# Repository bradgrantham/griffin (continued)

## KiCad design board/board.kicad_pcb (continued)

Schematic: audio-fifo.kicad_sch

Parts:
C36, C37, C38, C39: 100nF; C_Disc_D5.0mm_W2.5mm_P5.00mm
R35, R36, R37, R38, R150, R151, R152, R153: 0R; R_Axial_DIN0207_L6.3mm_D2.5mm_P10.16mm_Horizontal
TP3, TP4, TP5, TP6: TestPoint; TestPoint_Pad_D1.5mm
U25, U26, U30, U31: IDT7200L15P; DIP-28_W7.62mm

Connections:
+5V: C36.1, C37.1, C38.1, C39.1, U25.23 (FL), U25.28 (VCC), U26.23 (FL), U26.28 (VCC), U30.23 (FL), U30.28 (VCC), U31.23 (FL), U31.28 (VCC); also elsewhere on the board
/AUDIO_FIFO/~SAMPLES0_FIFO_W_FIFO_SIDE: R150.2, U25.1 (WR)
/AUDIO_FIFO/~SAMPLES1_FIFO_W_FIFO_SIDE: R151.2, U26.1 (WR)
/AUDIO_FIFO/~SAMPLES2_FIFO_W_FIFO_SIDE: R152.2, U30.1 (WR)
/AUDIO_FIFO/~SAMPLES3_FIFO_W_FIFO_SIDE: R153.2, U31.1 (WR)
D_AUDIO_FIFO0: U30.6 (D0), U31.6 (D0); also elsewhere on the board
D_AUDIO_FIFO1: U30.5 (D1), U31.5 (D1); also elsewhere on the board
D_AUDIO_FIFO2: U30.4 (D2), U31.4 (D2); also elsewhere on the board
D_AUDIO_FIFO3: U30.3 (D3), U31.3 (D3); also elsewhere on the board
D_AUDIO_FIFO4: U30.27 (D4), U31.27 (D4); also elsewhere on the board
D_AUDIO_FIFO5: U30.26 (D5), U31.26 (D5); also elsewhere on the board
D_AUDIO_FIFO6: U30.25 (D6), U31.25 (D6); also elsewhere on the board
D_AUDIO_FIFO7: U30.24 (D7), U31.24 (D7); also elsewhere on the board
D_AUDIO_FIFO8: U25.6 (D0), U26.6 (D0); also elsewhere on the board
D_AUDIO_FIFO9: U25.5 (D1), U26.5 (D1); also elsewhere on the board
D_AUDIO_FIFO10: U25.4 (D2), U26.4 (D2); also elsewhere on the board
D_AUDIO_FIFO11: U25.3 (D3), U26.3 (D3); also elsewhere on the board
D_AUDIO_FIFO12: U25.27 (D4), U26.27 (D4); also elsewhere on the board
D_AUDIO_FIFO13: U25.26 (D5), U26.26 (D5); also elsewhere on the board
D_AUDIO_FIFO14: U25.25 (D6), U26.25 (D6); also elsewhere on the board
D_AUDIO_FIFO15: U25.24 (D7), U26.24 (D7); also elsewhere on the board
GND: C36.2, C37.2, C38.2, C39.2, U25.2 (D8), U25.7 (XI), U25.14 (VSS), U26.2 (D8), U26.7 (XI), U26.14 (VSS), U30.2 (D8), U30.7 (XI), U30.14 (VSS), U31.2 (D8), U31.7 (XI), U31.14 (VSS); also elsewhere on the board
unnamed: R35.1, U25.15 (RD)
unnamed: R36.1, U26.15 (RD)
unnamed: R37.1, U30.15 (RD)
unnamed: R38.1, U31.15 (RD)
SAMPLE0_Q0: U25.9 (Q0); also elsewhere on the board
SAMPLE0_Q1: U25.10 (Q1); also elsewhere on the board
SAMPLE0_Q2: U25.11 (Q2); also elsewhere on the board
SAMPLE0_Q3: U25.12 (Q3); also elsewhere on the board
SAMPLE0_Q4: U25.16 (Q4); also elsewhere on the board
SAMPLE0_Q5: U25.17 (Q5); also elsewhere on the board
SAMPLE0_Q6: U25.18 (Q6); also elsewhere on the board
SAMPLE0_Q7: U25.19 (Q7); also elsewhere on the board
SAMPLE1_Q0: U26.9 (Q0); also elsewhere on the board
SAMPLE1_Q1: U26.10 (Q1); also elsewhere on the board
SAMPLE1_Q2: U26.11 (Q2); also elsewhere on the board
SAMPLE1_Q3: U26.12 (Q3); also elsewhere on the board
SAMPLE1_Q4: U26.16 (Q4); also elsewhere on the board
SAMPLE1_Q5: U26.17 (Q5); also elsewhere on the board
SAMPLE1_Q6: U26.18 (Q6); also elsewhere on the board
SAMPLE1_Q7: U26.19 (Q7); also elsewhere on the board
SAMPLE2_Q0: U30.9 (Q0); also elsewhere on the board
SAMPLE2_Q1: U30.10 (Q1); also elsewhere on the board
SAMPLE2_Q2: U30.11 (Q2); also elsewhere on the board
SAMPLE2_Q3: U30.12 (Q3); also elsewhere on the board
SAMPLE2_Q4: U30.16 (Q4); also elsewhere on the board
SAMPLE2_Q5: U30.17 (Q5); also elsewhere on the board
SAMPLE2_Q6: U30.18 (Q6); also elsewhere on the board
SAMPLE2_Q7: U30.19 (Q7); also elsewhere on the board
SAMPLE3_Q0: U31.9 (Q0); also elsewhere on the board
SAMPLE3_Q1: U31.10 (Q1); also elsewhere on the board
SAMPLE3_Q2: U31.11 (Q2); also elsewhere on the board
SAMPLE3_Q3: U31.12 (Q3); also elsewhere on the board
SAMPLE3_Q4: U31.16 (Q4); also elsewhere on the board
SAMPLE3_Q5: U31.17 (Q5); also elsewhere on the board
SAMPLE3_Q6: U31.18 (Q6); also elsewhere on the board
SAMPLE3_Q7: U31.19 (Q7); also elsewhere on the board
~RESET: U25.22 (CLR), U26.22 (CLR), U30.22 (CLR), U31.22 (CLR); also elsewhere on the board
~SAMPLES0_FIFO_W: R150.1; also elsewhere on the board
~SAMPLES1_FIFO_W: R151.1; also elsewhere on the board
~SAMPLES2_FIFO_W: R152.1; also elsewhere on the board
~SAMPLES3_FIFO_W: R153.1; also elsewhere on the board
~SAMPLE_EF0: TP3.1, U25.21 (EF); also elsewhere on the board
~SAMPLE_EF1: TP4.1, U26.21 (EF); also elsewhere on the board
~SAMPLE_EF2: TP5.1, U30.21 (EF); also elsewhere on the board
~SAMPLE_EF3: TP6.1, U31.21 (EF); also elsewhere on the board
~SAMPLE_R0: R35.2; also elsewhere on the board
~SAMPLE_R1: R36.2; also elsewhere on the board
~SAMPLE_R2: R37.2; also elsewhere on the board
~SAMPLE_R3: R38.2; also elsewhere on the board

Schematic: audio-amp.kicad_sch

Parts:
C57, C59, C61: 47nF; C_Rect_L7.2mm_W2.5mm_P5.00mm
C58, C60, C62: 250uF; CP_Radial_D8.0mm_P3.50mm
C65, C66, C67: 100nF; C_Disc_D5.0mm_W2.5mm_P5.00mm
J6: 3.5mm stereo, tip+ring NC switches (part TBD: SJ3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
J16: VOLUME POT (dual 10kA, panel); PinHeader_1x06_P2.54mm_Vertical
J17: SPEAKER 8 ohm (case); PinHeader_1x02_P2.54mm_Vertical
R91, R94: 10k; R_Axial_DIN0207_L6.3mm_D2.5mm_P10.16mm_Horizontal
R92, R95, R99: 1k; R_Axial_DIN0207_L6.3mm_D2.5mm_P10.16mm_Horizontal
R93, R96, R154: 10R; R_Axial_DIN0207_L6.3mm_D2.5mm_P10.16mm_Horizontal
R97, R98: 47k; R_Axial_DIN0207_L6.3mm_D2.5mm_P10.16mm_Horizontal
U33, U34, U35: LM386; DIP-8_W7.62mm

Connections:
+5V: C65.1, C66.1, C67.1, U33.6 (V+), U34.6 (V+), U35.6 (V+); also elsewhere on the board
/AUDIO_AMP/HP_AMP_L: C58.1, R93.1, U33.5
/AUDIO_AMP/HP_AMP_R: C60.1, R96.1, U34.5
/AUDIO_AMP/HP_IN_L: R91.2, R92.1, U33.3 (+)
/AUDIO_AMP/HP_IN_R: R94.2, R95.1, U34.3 (+)
/AUDIO_AMP/POT_L: J16.2, R91.1
/AUDIO_AMP/POT_R: J16.5, R94.1
/AUDIO_AMP/SPK_AMP: C62.1, R154.1, U35.5
/AUDIO_AMP/SPK_IN_L: J6.TN, R97.1
/AUDIO_AMP/SPK_IN_R: J6.RN, R98.1
/AUDIO_AMP/SPK_PLUS: C62.2, J17.1
/AUDIO_AMP/SPK_SUM: R97.2, R98.2, R99.1, U35.3 (+)
/AUDIO_AMP/ZOB_L: C57.1, R93.2
/AUDIO_AMP/ZOB_R: C59.1, R96.2
/AUDIO_AMP/ZOB_SPK: C61.1, R154.2
GND: C57.2, C59.2, C61.2, C65.2, C66.2, C67.2, J6.S, J16.3, J16.6, J17.2, R92.2, R95.2, R99.2, U33.2 (-), U33.4 (GND), U34.2 (-), U34.4 (GND), U35.2 (-), U35.4 (GND); also elsewhere on the board
HP_L: C58.2, J6.T
HP_R: C60.2, J6.R
LINE_L: J16.1; also elsewhere on the board
LINE_R: J16.4; also elsewhere on the board

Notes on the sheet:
Inserting a plug opens TN/RN and mutes the speaker; software mute = VOLUME 0 on all four channels (griffin.yml).
C65, C66, C67 bypass U33, U34, U35. R154 is the speaker Zobel 10R.
J16: dual-gang 10k audio taper, element top = LINE, bottom = GND, wiper out; panel part on a header.

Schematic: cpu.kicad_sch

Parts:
C2, C3: 100nF; C_Disc_D5.0mm_W2.5mm_P5.00mm
R4, R5, R6, R8, R9, R10, R11, R12, R13, R14: 10K; R_Axial_DIN0207_L6.3mm_D2.5mm_P10.16mm_Horizontal
R7: 4.7K; R_Axial_DIN0207_L6.3mm_D2.5mm_P10.16mm_Horizontal
U2: MC68000; DIP-64_W22.86mm

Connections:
+5V: C2.1, C3.1, R4.1, R5.1, R6.1, R7.1, R8.1, R9.1, R10.1, R11.1, R12.1, R13.1, R14.1, U2.14 (V_{CC}), U2.49 (V_{CC}); also elsewhere on the board
A1: U2.29 (A1); also elsewhere on the board
A2: U2.30 (A2); also elsewhere on the board
A3: U2.31 (A3); also elsewhere on the board
A4: U2.32 (A4); also elsewhere on the board
A5: U2.33 (A5); also elsewhere on the board
A6: U2.34 (A6); also elsewhere on the board
A7: U2.35 (A7); also elsewhere on the board
A8: U2.36 (A8); also elsewhere on the board
A9: U2.37 (A9); also elsewhere on the board
A10: U2.38 (A10); also elsewhere on the board
A11: U2.39 (A11); also elsewhere on the board
A12: U2.40 (A12); also elsewhere on the board
A13: U2.41 (A13); also elsewhere on the board
A14: U2.42 (A14); also elsewhere on the board
A15: U2.43 (A15); also elsewhere on the board
A16: U2.44 (A16); also elsewhere on the board
A17: U2.45 (A17); also elsewhere on the board
A18: U2.46 (A18); also elsewhere on the board
A19: U2.47 (A19); also elsewhere on the board
A20: U2.48 (A20); also elsewhere on the board
A21: U2.50 (A21); also elsewhere on the board
A22: U2.51 (A22); also elsewhere on the board
A23: U2.52 (A23); also elsewhere on the board
D0: U2.5 (D0); also elsewhere on the board
D1: U2.4 (D1); also elsewhere on the board
D2: U2.3 (D2); also elsewhere on the board
D3: U2.2 (D3); also elsewhere on the board
D4: U2.1 (D4); also elsewhere on the board
D5: U2.64 (D5); also elsewhere on the board
D6: U2.63 (D6); also elsewhere on the board
D7: U2.62 (D7); also elsewhere on the board
D8: U2.61 (D8); also elsewhere on the board
D9: U2.60 (D9); also elsewhere on the board
D10: U2.59 (D10); also elsewhere on the board
D11: U2.58 (D11); also elsewhere on the board
D12: U2.57 (D12); also elsewhere on the board
D13: U2.56 (D13); also elsewhere on the board
D14: U2.55 (D14); also elsewhere on the board
D15: U2.54 (D15); also elsewhere on the board
FC0: R6.2, U2.28 (FC0); also elsewhere on the board
FC1: R9.2, U2.27 (FC1); also elsewhere on the board
FC2: R11.2, U2.26 (FC2); also elsewhere on the board
GND: C2.2, C3.2, U2.16 (GND), U2.53 (GND); also elsewhere on the board
R/~W: R10.2, U2.9 (R/~W); also elsewhere on the board
SYSCLK: U2.15 (CLK); also elsewhere on the board
~AS: R8.2, U2.6 (~AS); also elsewhere on the board
~BERR: U2.22 (~BERR); also elsewhere on the board
~BGACK: R5.2, U2.12 (~BGACK); also elsewhere on the board
~BG: U2.11 (~BG); also elsewhere on the board
~BR: R4.2, U2.13 (~BR); also elsewhere on the board
~DTACK: U2.10 (~DTACK); also elsewhere on the board
~HALT: R7.2, U2.17 (~HALT); also elsewhere on the board
~IPL0: U2.25 (~IPL0); also elsewhere on the board
~IPL1: U2.24 (~IPL1); also elsewhere on the board
~IPL2: U2.23 (~IPL2); also elsewhere on the board
~LDS: R13.2, U2.8 (~LDS); also elsewhere on the board
~RESET: U2.18 (~RESET); also elsewhere on the board
~UDS: R12.2, U2.7 (~UDS); also elsewhere on the board
~VPA: R14.2, U2.21 (~VPA); also elsewhere on the board

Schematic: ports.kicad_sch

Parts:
C17: 100nF; C_Disc_D5.0mm_W2.5mm_P5.00mm
J13: PORTS SPARE; PinHeader_1x03_P2.54mm_Vertical
U14: PORTS; PLCC-84_THT-Socket

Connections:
+5V: C17.1, U14.3 (VCCINT), U14.13 (VCCIO), U14.26 (VCCIO), U14.38 (VCCIO), U14.43 (VCCINT), U14.53 (VCCIO), U14.66 (VCCIO), U14.78 (VCCIO); also elsewhere on the board
/PORTS/PORTS_SPARE_34: J13.1, U14.34 (I/O)
/PORTS/PORTS_SPARE_41: J13.2, U14.41 (I/O)
A1: U14.31 (I/O); also elsewhere on the board
A2: U14.30 (I/O); also elsewhere on the board
A3: U14.21 (I/O); also elsewhere on the board
A4: U14.22 (I/O); also elsewhere on the board
D0: U14.18 (I/O); also elsewhere on the board
D1: U14.16 (I/O); also elsewhere on the board
D2: U14.15 (I/O); also elsewhere on the board
D3: U14.28 (I/O); also elsewhere on the board
D4: U14.24 (I/O); also elsewhere on the board
D5: U14.27 (I/O); also elsewhere on the board
D6: U14.20 (I/O); also elsewhere on the board
D7: U14.29 (I/O); also elsewhere on the board
GLUE_TO_PORTS_TD: U14.14 (I/O/TDI); also elsewhere on the board
GND: C17.2, J13.3, U14.7 (GND), U14.19 (GND), U14.32 (GND), U14.42 (GND), U14.47 (GND), U14.59 (GND), U14.72 (GND), U14.82 (GND); also elsewhere on the board
JOYSTICK_1_DOWN: U14.12 (I/O/PD1); also elsewhere on the board
JOYSTICK_1_FIRE: U14.40 (I/O); also elsewhere on the board
JOYSTICK_1_LEFT: U14.51 (I/O); also elsewhere on the board
JOYSTICK_1_PIN5: U14.5 (I/O); also elsewhere on the board
JOYSTICK_1_PIN9: U14.39 (I/O); also elsewhere on the board
JOYSTICK_1_RIGHT: U14.35 (I/O); also elsewhere on the board
JOYSTICK_1_UP: U14.9 (I/O); also elsewhere on the board
JOYSTICK_2_DOWN: U14.11 (I/O); also elsewhere on the board
JOYSTICK_2_FIRE: U14.4 (I/O); also elsewhere on the board
JOYSTICK_2_LEFT: U14.50 (I/O); also elsewhere on the board
JOYSTICK_2_PIN5: U14.8 (I/O); also elsewhere on the board
JOYSTICK_2_PIN9: U14.37 (I/O); also elsewhere on the board
JOYSTICK_2_RIGHT: U14.36 (I/O); also elsewhere on the board
JOYSTICK_2_UP: U14.10 (I/O); also elsewhere on the board
JTAG_TCK: U14.62 (I/O/TCK); also elsewhere on the board
JTAG_TMS: U14.23 (I/O/TMS); also elsewhere on the board
PADDLE_DUMP: U14.33 (I/O); also elsewhere on the board
PADDLE_TICK: U14.44 (I/O); also elsewhere on the board
PORTS_TO_AUDIO_TD: U14.71 (I/O/TDO); also elsewhere on the board
PS2_MOUSE_CLK: U14.81 (I/O/GCLK3); also elsewhere on the board
PS2_MOUSE_DATA: U14.80 (I/O); also elsewhere on the board
R/~W: U14.25 (I/O); also elsewhere on the board
SYSCLK: U14.83 (INPUT/GCLK1); also elsewhere on the board
~LDS: U14.2 (INPUT/OE2/GCLK2); also elsewhere on the board
~PORTS_IRQ: U14.17 (I/O); also elsewhere on the board
~PORTS_SELECT: U14.49 (I/O); also elsewhere on the board
~RESET: U14.6 (I/O); also elsewhere on the board

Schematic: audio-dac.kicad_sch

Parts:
C52: 10uF; CP_Radial_D5.0mm_P2.00mm
C53, C54: 8.2nF; C_Rect_L7.2mm_W2.5mm_P5.00mm
C55, C56: 100uF; CP_Radial_D6.3mm_P2.50mm
C63, C64: 100nF; C_Disc_D5.0mm_W2.5mm_P5.00mm
J14: RCA LINE OUT L; CUI_RCJ-044
J15: RCA LINE OUT R; CUI_RCJ-044
R22, R80, R81, R82: 4610X-R2R-103LF; BO_4610X
R83, R84: 10k; R_Axial_DIN0207_L6.3mm_D2.5mm_P10.16mm_Horizontal
R85, R86: 2k; R_Axial_DIN0207_L6.3mm_D2.5mm_P10.16mm_Horizontal
R87, R88: 4.7k; R_Axial_DIN0207_L6.3mm_D2.5mm_P10.16mm_Horizontal
R89, R90: 100R; R_Axial_DIN0207_L6.3mm_D2.5mm_P10.16mm_Horizontal
U17: LM358; DIP-8_W7.62mm
U32: 74HC4066; DIP-14_W7.62mm

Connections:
+5V: C63.1, C64.1, R83.1, U17.8 (V+), U32.14 (VDD); also elsewhere on the board
/AUDIO_DAC/AMP_L: C53.2, C55.1, R85.2, R87.1, U17.1
/AUDIO_DAC/AMP_R: C54.2, C56.1, R86.2, R88.1, U17.7
/AUDIO_DAC/LADDER_0: R22.1, U32.1
/AUDIO_DAC/LADDER_1: R80.1, U32.4
/AUDIO_DAC/LADDER_2: R81.1, U32.8
/AUDIO_DAC/LADDER_3: R82.1, U32.11
/AUDIO_DAC/RCA_L: J14.1 (In), R89.2
/AUDIO_DAC/RCA_R: J15.1 (In), R90.2
/AUDIO_DAC/SUM_L: C53.1, R85.1, U17.2 (-), U32.2, U32.3
/AUDIO_DAC/SUM_R: C54.1, R86.1, U17.6 (-), U32.9, U32.10
/AUDIO_DAC/VBIAS: C52.1, R83.2, R84.1, U17.3 (+), U17.5 (+)
GATE0: U32.13; also elsewhere on the board
GATE1: U32.5; also elsewhere on the board
GATE2: U32.6; also elsewhere on the board
GATE3: U32.12; also elsewhere on the board
GND: C52.2, C63.2, C64.2, J14.2 (Ext), J15.2 (Ext), R22.10, R80.10, R81.10, R82.10, R84.2, R87.2, R88.2, U17.4 (V-), U32.7 (VSS); also elsewhere on the board
LINE_L: C55.2, R89.1; also elsewhere on the board
LINE_R: C56.2, R90.1; also elsewhere on the board
SAMPLE0_Q0: R22.9; also elsewhere on the board
SAMPLE0_Q1: R22.8; also elsewhere on the board
SAMPLE0_Q2: R22.7; also elsewhere on the board
SAMPLE0_Q3: R22.6; also elsewhere on the board
SAMPLE0_Q4: R22.5; also elsewhere on the board
SAMPLE0_Q5: R22.4; also elsewhere on the board
SAMPLE0_Q6: R22.3; also elsewhere on the board
SAMPLE0_Q7: R22.2; also elsewhere on the board
SAMPLE1_Q0: R80.9; also elsewhere on the board
SAMPLE1_Q1: R80.8; also elsewhere on the board
SAMPLE1_Q2: R80.7; also elsewhere on the board
SAMPLE1_Q3: R80.6; also elsewhere on the board
SAMPLE1_Q4: R80.5; also elsewhere on the board
SAMPLE1_Q5: R80.4; also elsewhere on the board
SAMPLE1_Q6: R80.3; also elsewhere on the board
SAMPLE1_Q7: R80.2; also elsewhere on the board
SAMPLE2_Q0: R81.9; also elsewhere on the board
SAMPLE2_Q1: R81.8; also elsewhere on the board
SAMPLE2_Q2: R81.7; also elsewhere on the board
SAMPLE2_Q3: R81.6; also elsewhere on the board
SAMPLE2_Q4: R81.5; also elsewhere on the board
SAMPLE2_Q5: R81.4; also elsewhere on the board
SAMPLE2_Q6: R81.3; also elsewhere on the board
SAMPLE2_Q7: R81.2; also elsewhere on the board
SAMPLE3_Q0: R82.9; also elsewhere on the board
SAMPLE3_Q1: R82.8; also elsewhere on the board
SAMPLE3_Q2: R82.7; also elsewhere on the board
SAMPLE3_Q3: R82.6; also elsewhere on the board
SAMPLE3_Q4: R82.5; also elsewhere on the board
SAMPLE3_Q5: R82.4; also elsewhere on the board
SAMPLE3_Q6: R82.3; also elsewhere on the board
SAMPLE3_Q7: R82.2; also elsewhere on the board

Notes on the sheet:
Offset-binary samples: 0x80 = 2.5 V = silence; no inverter, no pulls on Q. Summer biased at VBIAS 2.5 V, 2k || 8.2 nF (pole ~9.7 kHz), 4.7k class-A bias, 100 uF to LINE. Line out fixed level ~0.88 Vrms. Not yet breadboarded (griffin.yml issues). C63 bypasses U32, C64 bypasses U17.

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
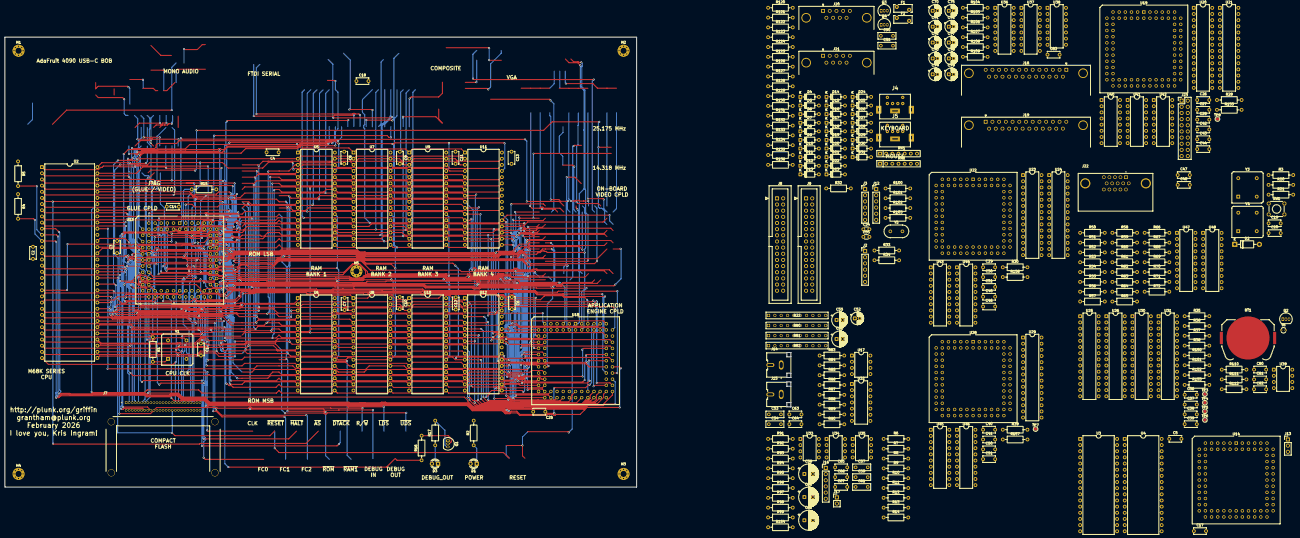
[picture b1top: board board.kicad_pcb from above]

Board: 4 copper layers, 324.3 x 185.6 mm, 305 parts (0 on the bottom side), 443 nets.

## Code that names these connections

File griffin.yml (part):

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        width: 8
        description: |
          Set or clear DEBUG_OUT signal (debug LED and test point output).
          While ~HALT is low GLUE overrides the pin with a ~1.9 Hz blink
          (vsync/32); the register value returns when ~HALT releases.
        bits:
          - { bit: "0", name: OUT, description: "DEBUG_OUT drive level" }
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          - { bit: "4", name: RX_FRAME_ERR,
              description: "1 = framing error" }
          - { bit: "5", name: DATA_LIVE,
              description: "Unlatched synchronized PS2_DATA pin state (debug)" }
          - { bit: "6", name: CLK_LIVE,
              description: "Debounced PS2_CLK level the frame engine clocks on, not the raw pin (debug)" }
      - offset: 0x11
        name: PS2_CLEAR
        access: write
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      section: ram

  # nENGINE_SELECT comes from GLUE, which also owns DTACK for the CPU's
  # DESC/CTRL writes (0 wait states); ENGINE has no DTACK pin.  As a master
  # it does not sample DTACK either: every source it reads is 0-wait-state
  # SRAM selected combinationally from the address.
  # Write-only MMIO decoded on A[2:1] with LDS; reads see the open bus, so
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          - { bit: "4", name: RX_FRAME_ERR,
              description: "1 = framing error" }
          - { bit: "5", name: DATA_LIVE,
              description: "Unlatched synchronized PS2_MOUSE_DATA pin state (debug)" }
          - { bit: "6", name: CLK_LIVE,
              description: "Debounced PS2_MOUSE_CLK level the frame engine clocks on, not the raw pin (debug)" }
      - offset: 0x11
        name: PS2_MOUSE_CLEAR
        access: write
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          - { bit: "7:0", name: DATA, description: "Received packet byte" }

  # 16-bit True IDE PIO.  GLUE gates IOWR with AS.  Sideband pins INTRQ and
  # IORDY go to GLUE (see GLUE CF_PINS).  The dtack entries below are the
  # fixed part of the cycle; IORDY extends it.
  CF:
    part: "Compact Flash (True IDE)"
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    #   OP3: RTC_SDA_DRIVE (N-FET gate: pin high pulls SDA low)
    #                                            IP2: RTC_SDA readback
    #                                            IP3: RTC_MFP (MCP7940N MFP, firmware programs it as the 1 Hz square wave)
    #   OP4..OP7: PIXEL reserved pins (no logic) IP4: DCD_B (ch B carrier)
    #                                            IP5: RI_B (ch B ring)
    # IP4/IP5 come from the ch B RS-232 receivers; the 68681
    # change-of-state IRQ covers only IP0-IP3, so both are poll-only.
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# Rev 1 board reworks (applied to board/board-pcb-rev-1.distilled.txt).
bodges:
  - "Reroute A6 pad on U12 to A18"
  - "Route freed GLUE pin 75 to CPU ~VPA"
  - "Pull up CPU HALT with 4.7K to nearby CPU +5V"

# Open items only.
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    grounded) into DUART IP4/IP5.
    Ch A console: DB-25 FEMALE wired DCE.  Pin 2 -> receiver -> RXDA;
    TXDA -> driver -> pin 3; pin 4 (terminal RTS) -> receiver -> IP0
    (~CTS_A); OP0 (~RTS_A) -> driver -> pin 5 (terminal CTS); strap DSR
    (6) and DCD (8) to the terminal's DTR (20) at the connector; pin 7
    signal ground.
    Ch B modem port: DB-25 MALE wired DTE.  TXDB -> driver -> pin 2;
    pin 3 -> receiver -> RXDB; OP1 (~RTS_B) -> driver -> pin 4; pin 5 ->
    receiver -> IP1 (~CTS_B); pin 8 (DCD) -> 75189 -> IP4; pin 22 (RI)
    -> 75189 -> IP5; DTR (20) strapped to DSR (6) at the connector (a
    GLUE bodge spare can drive DTR later if ever wanted); pin 7 signal
    ground.
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
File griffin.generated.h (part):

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static constexpr uint32_t GLUE_SIZE = 0x040000UL;
inline constexpr MemoryRange GLUE(0xF00000UL, 0x040000UL);
static constexpr uint32_t GLUE_IRQ_LEVEL = 4U;
static constexpr int GLUE_BERR_TIMEOUT_CLOCKS = 15;  // SYSCLK edges after ~AS with no DTACK
static constexpr int GLUE_DTACK_WS = 0;  // wait states at 14000000 Hz
static constexpr int GLUE_DTACK_THRESHOLD = 2;  // ws_cnt threshold for Verilog
static constexpr int GLUE_DTACK_PENALTY = 0;  // extra SYSCLK cycles for emulator
static constexpr uint32_t GLUE_DEBUG_OUT = 0xF00001UL;  // WRITE: Set or clear DEBUG_OUT signal (debug LED and test point output)
static constexpr uint32_t GLUE_DEBUG_OUT_MASK  = 0x01U;  // bits 0:0
static constexpr uint32_t GLUE_DEBUG_OUT_SHIFT = 0U;
static constexpr uint32_t GLUE_CONFIG = 0xF00007UL;  // WRITE: GLUE configuration register
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static constexpr uint32_t GLUE_PS2_CLEAR_RX_READY_SHIFT = 0U;
static constexpr uint32_t GLUE_PS2_CLEAR_TX_DONE_MASK  = 0x02U;  // bits 1:1
static constexpr uint32_t GLUE_PS2_CLEAR_TX_DONE_SHIFT = 1U;
static constexpr uint32_t GLUE_PS2_CTRL = 0xF00013UL;  // WRITE: Open-drain drive control for PS2_CLK and PS2_DATA for the TX inhibit handshake
static constexpr uint32_t GLUE_PS2_CTRL_CLK_MASK  = 0x01U;  // bits 0:0
static constexpr uint32_t GLUE_PS2_CTRL_CLK_SHIFT = 0U;
static constexpr uint32_t GLUE_PS2_CTRL_DATA_MASK  = 0x02U;  // bits 1:1
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inline constexpr MemoryRange ROM(0x800000UL, 0x400000UL);
static constexpr int ROM_DTACK_WS = 1;  // wait states at 14000000 Hz
static constexpr int ROM_DTACK_THRESHOLD = 4;  // ws_cnt threshold for Verilog
static constexpr int ROM_DTACK_PENALTY = 2;  // extra SYSCLK cycles for emulator

// ------------------------------------------------------------
// RAM_BANK_1: 2x AS6C4008
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inline constexpr MemoryRange RAM_BANK_1(0x000000UL, 0x100000UL);
static constexpr int RAM_BANK_1_DTACK_WS = 0;  // wait states at 14000000 Hz
static constexpr int RAM_BANK_1_DTACK_THRESHOLD = 2;  // ws_cnt threshold for Verilog
static constexpr int RAM_BANK_1_DTACK_PENALTY = 0;  // extra SYSCLK cycles for emulator

// ------------------------------------------------------------
// RAM_BANK_2: 2x AS6C4008
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inline constexpr MemoryRange RAM_BANK_2(0x100000UL, 0x100000UL);
static constexpr int RAM_BANK_2_DTACK_WS = 0;  // wait states at 14000000 Hz
static constexpr int RAM_BANK_2_DTACK_THRESHOLD = 2;  // ws_cnt threshold for Verilog
static constexpr int RAM_BANK_2_DTACK_PENALTY = 0;  // extra SYSCLK cycles for emulator

// ------------------------------------------------------------
// RAM_BANK_3: 2x AS6C4008
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inline constexpr MemoryRange RAM_BANK_3(0x200000UL, 0x100000UL);
static constexpr int RAM_BANK_3_DTACK_WS = 0;  // wait states at 14000000 Hz
static constexpr int RAM_BANK_3_DTACK_THRESHOLD = 2;  // ws_cnt threshold for Verilog
static constexpr int RAM_BANK_3_DTACK_PENALTY = 0;  // extra SYSCLK cycles for emulator

// ------------------------------------------------------------
// RAM_BANK_4: 2x AS6C4008
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inline constexpr MemoryRange RAM_BANK_4(0x300000UL, 0x100000UL);
static constexpr int RAM_BANK_4_DTACK_WS = 0;  // wait states at 14000000 Hz
static constexpr int RAM_BANK_4_DTACK_THRESHOLD = 2;  // ws_cnt threshold for Verilog
static constexpr int RAM_BANK_4_DTACK_PENALTY = 0;  // extra SYSCLK cycles for emulator

// ------------------------------------------------------------
// ENGINE: Display-list DMA engine walking 4-word descriptors from the top 64K of RAM
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static constexpr uint32_t ENGINE_IRQ_LEVEL = 3U;
static constexpr int ENGINE_DTACK_WS = 0;  // wait states at 14000000 Hz
static constexpr int ENGINE_DTACK_THRESHOLD = 2;  // ws_cnt threshold for Verilog
static constexpr int ENGINE_DTACK_PENALTY = 0;  // extra SYSCLK cycles for emulator
static constexpr uint32_t ENGINE_DESC = 0xD00002UL;  // WRITE: Descriptor word address within RAM's top 64K; writing arms DMA
static constexpr uint32_t ENGINE_DESC_ADDR_MASK  = 0x7FFFU;  // bits 14:0
static constexpr uint32_t ENGINE_DESC_ADDR_SHIFT = 0U;
static constexpr uint32_t ENGINE_CTRL = 0xD00005UL;  // WRITE: DMA enable and abort; any write clears a pending ~ENGINE_IRQ
static constexpr uint32_t ENGINE_CTRL_ENABLE_MASK  = 0x01U;  // bits 0:0
static constexpr uint32_t ENGINE_CTRL_ENABLE_SHIFT = 0U;
static constexpr uint32_t ENGINE_CTRL_DEFAULT = 0x00U;
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static constexpr uint32_t PORTS_IRQ_LEVEL = 2U;
static constexpr int PORTS_DTACK_WS = 0;  // wait states at 14000000 Hz
static constexpr int PORTS_DTACK_THRESHOLD = 2;  // ws_cnt threshold for Verilog
static constexpr int PORTS_DTACK_PENALTY = 0;  // extra SYSCLK cycles for emulator
static constexpr uint32_t PORTS_JOYSTICK_PORT_1 = 0xFC0001UL;  // READ: Joystick port 1 switches, active low (0 = closed)
static constexpr uint32_t PORTS_JOYSTICK_PORT_1_UP_MASK  = 0x01U;  // bits 0:0
static constexpr uint32_t PORTS_JOYSTICK_PORT_1_UP_SHIFT = 0U;
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static constexpr uint32_t PORTS_PS2_MOUSE_CLEAR_RX_READY_SHIFT = 0U;
static constexpr uint32_t PORTS_PS2_MOUSE_CLEAR_TX_DONE_MASK  = 0x02U;  // bits 1:1
static constexpr uint32_t PORTS_PS2_MOUSE_CLEAR_TX_DONE_SHIFT = 1U;
static constexpr uint32_t PORTS_PS2_MOUSE_CTRL = 0xFC0013UL;  // WRITE: Open-drain drive control for PS2_MOUSE_CLK and PS2_MOUSE_DATA for the TX inhibit handshake
static constexpr uint32_t PORTS_PS2_MOUSE_CTRL_CLK_MASK  = 0x01U;  // bits 0:0
static constexpr uint32_t PORTS_PS2_MOUSE_CTRL_CLK_SHIFT = 0U;
static constexpr uint32_t PORTS_PS2_MOUSE_CTRL_DATA_MASK  = 0x02U;  // bits 1:1
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static constexpr uint32_t CF_IRQ_LEVEL = 1U;
static constexpr int CF_DTACK_WS = 7;  // wait states at 14000000 Hz
static constexpr int CF_DTACK_THRESHOLD = 14;  // ws_cnt threshold for Verilog
static constexpr int CF_DTACK_PENALTY = 12;  // extra SYSCLK cycles for emulator
static constexpr uint32_t CF_DATA = 0xF40000UL;  // RW: 16-bit data port to/from the CF card
static constexpr uint32_t CF_ERROR = 0xF40003UL;  // READ: Error register
static constexpr uint32_t CF_FEATURES = 0xF40003UL;  // WRITE: Features register
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
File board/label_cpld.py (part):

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nets come from --pin (or from cpld_map.py's jtag entry).

With --chip NAME everything comes from cpld_map.py: Verilog, sheet, symbol,
renames, the JTAG nets (pins 23/62 are always JTAG_TMS/JTAG_TCK), fixed pins
(global labels), spare pins (local label <CHIP>_SPARE_<pin>) and leave pins
(untouched).  check_cpld_pins.py checks the result against the netlist.

Examples:
  label_cpld.py --chip ENGINE --relabel
  label_cpld.py --verilog ../cpld/engine/engine.v --sch engine.kicad_sch \
      --ref U18 --pin 14=AUDIO_TO_ENGINE_TD:input --pin 71=ENGINE_TO_PIXEL_TD:output \
      --pin 62=JTAG_TCK:input --pin 23=JTAG_TMS:input

Existing no-connects on the labeled pins are replaced; an existing wire or
label on a pin that would be labeled is an error (nothing is written) unless
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
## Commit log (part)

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2026-03-29 initial generated composite video controller
2026-03-29 commented out chunks for bringup diagnosis
2026-03-30 make 'maybe' section of board spin notes
2026-03-30 Don't translate C style to Verilog
2026-03-30 use GLUE UART, make beeps once
    * Switch to GLUE UART for all output
    * Make happy beeps on RAM test success
    * Make sad beeps on RAM test fail
2026-03-30 Add Verilog code style adapted from Alice 5 RISC V
2026-03-30 add initial compact flash support
    * add CF to emulator
    * add rom probe init of CF and dump first sector
2026-03-30 checkpoint VIDEO bringup tests
2026-03-30 Add verification target
2026-03-30 add TIMER register to GLUE
    * Add timer register to YAML
    * Implement timer in glue.v
    * Emulate timer in emulator.cpp
    * Use timer for tones in sanity.s
2026-03-30 fix timer
2026-03-30 Add programming manual for the hardware
2026-03-30 add files to ignore in IO MCU build
2026-03-30 add files to ignore in firmware build
2026-03-30 add files to ignore in sanity boot ROM build
2026-03-30 add files to ignore in GLUE CPLD build
2026-03-30 add files to ignore in CPLD upper
2026-03-30 add files to ignore in VIDEO CPLD build
2026-03-30 ignore netlists
2026-03-30 add files to ignore at top level
2026-03-30 add rev 1 netlist
2026-03-30 add one-off fixup script for CF symbol pins
2026-03-30 a CF card symbol
2026-03-30 add CF card footprint
2026-03-30 add build number to GLUE bitfile
2026-03-30 clarify ROM and IO MCU in board rev
2026-03-30 manage encoded version better
2026-03-30 add sanity testing to ROM firmware
    * Add exception handlers that blink
    * Wait for HALT to settle with a loop
    * Set DEBUG_OUT high at end of startup, otherwise breaks UART encoding
    * Add memory test
    * Add GLUE build ID
2026-03-31 Add a startup sound
    * Add play_audio() function that uses GLUE_TIMER stall to clock audio writes
    * Link in startup.raw and play it
2026-03-31 rev 2 use a 16-bit ROM, pull up on all DTACKs
2026-03-31 add identity string
2026-03-31 add IO MCU identity, add compiled clock freq
2026-03-31 add IO MCU ID, clock MHz, startup sound, emulator audio (broken)
2026-03-31 fix IO ID, purge SDL, use Hz for clock
2026-03-31 pullup PS/2 CLKs in case INT pullups insufficient
2026-03-31 remove speed reg, reduce build to 8 bits, improve CF
2026-03-31 add more diagnostics on CF card
2026-03-31 fire irq on IDENTITY, fix long TX block on bus
2026-03-31 add some revision notes re: CF card
2026-04-03 add debug prints
2026-04-03 Add CF card probe and listing
2026-04-03 add debug prints on IO processor ISR
2026-04-03 clean up bus handshake handling
2026-04-03 hook up signals to GLUE and bus and set to disabled or tristate
2026-04-03 initial debug_in uart rx (untested)
2026-04-03 more design, notes about IO-MCU
2026-04-03 print what's on the bus before driving it
2026-04-03 move IO-MCU functionality to GLUE
    * Add a systick timer to GLUE
    * Drop UART RX from GLUE
2026-04-03 more ideas about I/O
2026-04-03 simplify and then extend GLUE to handle some IO functions
    * remove UART TX - bitbang using GLUE_TIMER
    * remove traces of UART RX - bitbang using GLUE_TIMER
    * replace IO IRQ with GLUE IRQ
    * add system tick and IRQ
    * mark IO absent
2026-04-03 extend emulator to handle new GLUE functionality
2026-04-03 use GLUE_TIMER to bitbang UART TX, handle UART RX
2026-04-04 note bitbanged TIMER RX and TX are working
2026-04-04 remove IO_RESET
2026-04-04 remove nIO_IRQ
2026-04-04 remove nIO_DTACK
2026-04-04 remove nIO_SELECT - still have computation
2026-04-04 remove traces of IO_MCU
2026-04-04 remove traces of IO MCU and BUILD_ID
2026-04-04 move to loadable SYSTICK
2026-04-04 Revert "move to loadable SYSTICK"
    This reverts commit 15719b66014456c1fa72332819296052d1302863.
    Turns out it used *more* of the CPLD.
2026-04-04 add design guidance
2026-04-04 add defaults for bitfields
2026-04-04 only have 200Hz and 180Hz tick, use a config shadow
2026-04-04 initial generated report generator from fitter output
2026-04-05 fix AUDIO_LE name
2026-04-05 add enhanced fit report and some CPLD conclusions
2026-04-05 simplify systick
2026-04-05 move Rev 2 to after functionality to be less confusing
2026-04-05 add name of CPLD and add ENGINE
2026-04-05 bring IO MCU notes up to date
2026-04-05 Note that UART RX is polled
2026-04-05 initial ENGINE implementation
2026-04-06 fix VIDEO to cooperate with ENGINE, update machine spec
2026-04-06 tighten ENGINE/VIDEO/GLUE integration
2026-04-06 add VIDEO manual, move manuals to doc/
2026-04-06 remove two bodges that can run on existing traces
2026-04-06 allow finer grained fb address, 0 row stride
2026-04-06 add thoughts about HW vs SW
2026-04-06 don't implement build ID
2026-04-06 fix signaling issues
2026-04-06 rename magick to convert as provided by macports
2026-04-06 MSbit first
2026-04-06 update emulator; no IO mcu, add engine config
2026-04-06 add video DMA setup and splash screen
2026-04-07 don't emit on ENGINE_TDI
2026-04-07 kill all ENGINE lines that aren't used
2026-04-07 add target to flash ENGINE
2026-04-07 change name of PROBE_JTAG
2026-04-07 update to MSB-first
2026-04-07 emulated initial video
2026-04-07 change name of PROBE_JTAG, add PROBE_ENGINE
2026-04-07 add ATF1508 one-hot note
2026-04-07 break out fb variables and config func
2026-04-07 reformat
2026-04-07 allow video to start after setup
2026-04-07 shrink CLAUDE.md and extract some design guidance
2026-04-07 drop the startup audio
2026-04-07 move to 640x480
2026-04-07 update audio story
2026-04-07 drop build ID
2026-04-08 change TIMER to 8 bits & sysclk, use palette reg, mask irqs
2026-04-08 make VIDEO IRQ 6
2026-04-08 simplify guidance to reduce tokens
2026-04-08 note to build glue before making source changes
2026-04-08 note 4th CPLD ideas
2026-04-09 more test point notes
2026-04-09 use constants for ENGINE and GLUE DTACK
2026-04-09 remove references to HALT_REQ; with ENGINE removed this bootss at 14MHz
2026-04-09 restructure, start thinking Rev 2
2026-04-10 move some doc files to doc/
2026-04-10 clean up, reorganize, delete cruft, add some details
2026-04-11 remove BUILD ID
2026-04-12 add flurry of new design ideas
2026-04-13 fix formatting
2026-04-14 add 68681 DUART and tie to syscalls; implement in emulator
2026-04-16 interface to DUART
2026-04-16 add a speed debugging bit
2026-04-16 target erasable 27C512
2026-04-16 clean up YAML a hair
2026-04-16 restore bitbang polled getchar
2026-04-17 remove pedantic brace note
2026-04-17 clean up
2026-04-17 add debug input and boot monitor
2026-04-17 add raw stdin mode for debug UART RX
2026-04-18 clean up SDL, don't bother fclose(audio), add partial vsync irq
2026-04-18 move IRQ 6 to VIDEO
2026-04-18 remove splash from ROM for now to decrease flash duration
2026-04-18 add a bunch of debug to handlers, partial video irq
2026-04-18 cut video down to timing, add CLRINT
2026-04-18 make compilation stricter
2026-04-18 implement and use the video interrupt
2026-04-20 clean up spacing and typos
2026-04-20 clean up comments
2026-04-20 factor duart_received_ready so read non-blocking; cleanup
2026-04-20 provide more information on lots of vectors
2026-04-20 fix video interrupt
2026-04-20 checkpoint design
2026-04-21 add bus error decoder
2026-04-23 initial PS/2 support, init RX/TX works, RX is WIP
2026-04-23 decoder ring for bus faults
2026-04-25 checkpoint rev 2 thinking
2026-04-25 snapshot debugging the PS/2 implementation; not quite right
2026-04-26 make PS2 signal names shorter
2026-04-26 note temporaries in CPLD builds
2026-04-27 implement audio DMA through ENGINE CPLD
2026-04-27 note language preference
2026-04-27 state C++ standard
2026-04-27 redo PS2 into C so I can fix it; mostly works now
2026-04-27 add queue size constant to machine definition YAML
2026-04-27 update with newest 2.0 thinking
2026-04-28 clarify C++23, be more specific about ICs
2026-04-28 MC68681
2026-04-28 switch to 68681 systick
2026-05-03 deleted obsolete docs
2026-05-03 add forgotten ps2 sources
2026-05-03 checkpoint tightening of warnings
2026-05-03 upgrade to C23
2026-05-03 add a web page
2026-05-03 ignore some more temporaries and caches
2026-05-03 generate C++ hardware register references
2026-05-03 remove codegen of 8051 header
2026-05-03 remove IO-MCU firmware directory
2026-05-03 add generated reg refs
2026-05-05 stub out ENGINE implementation
2026-05-05 ignore temporaries
2026-05-08 checkpoint video development
2026-05-08 stub ENGINE IRQ
2026-05-08 update Rev 2.0 investigation and summary
2026-05-08 implement even and odd byte FIFOs
2026-05-08 add a platform ID
2026-05-08 add emulation of video CPLD - scanout, palette
2026-05-09 more rev2 investigation status
2026-05-09 restore DUART as XR68C681
2026-05-10 checkpoint bringup of DMA for video
2026-05-10 note XR68C681 installed
2026-05-11 gate CPU writes with AS
2026-05-11 implement DMA video in emulator
2026-05-12 load splash screen from CF card
2026-05-12 output splash blob
2026-05-12 handle using a block device as CF card
2026-05-12 make current
2026-05-13 start shift at top of frame; remove background
2026-05-13 add synchronizers for CDC signals
2026-05-13 turn on video after DUART; use printf; change palettes
2026-05-13 remove BACKGROUND register
2026-05-22 update to include video
2026-05-22 checkpoint Griffin notes
2026-05-23 add nm for 68k toolchain
2026-05-23 add initial text rendering, not tested
2026-05-23 set CT_CC_GCC_ENABLE_INITFINI_ARRAY
2026-05-24 fix static constructors
2026-05-24 fix banner
2026-05-24 add splash blob
2026-05-24 route debug and printf to textport; print badge
2026-05-28 move to more optimization
2026-05-28 optimize scrolling and cursor operation
2026-05-29 set FatFS to use extended filenames
2026-05-29 add draft per-line palette image viewer; fix memory size print
2026-06-02 emulate per-line palette write, approach hw correctness
2026-06-02 add per-line fg/bg image dithering tools
2026-06-03 ignore binaries and image artifacts
2026-06-03 Add video stats probe
2026-06-05 move to palette inline with framebuffer
2026-06-07 move to byte transfer for PS/2 in CPLD
2026-06-12 clarify rev2
2026-06-12 make the emulator debuggable by Claude
2026-06-19 enable 115200 baud using XR68C681
2026-06-19 implement PS/2 in GLUE; implement 115200 for XR68C681
2026-06-19 Add video FIFO wiring guide for PCB v1
2026-06-22 add audio experiment, probably come back to this as Rev 2 feature.
2026-06-22 checkpoint more PCB rev 2 work
2026-06-28 remove sanity ROM
2026-06-28 remove stale griffin.h
2026-06-28 add attribution for image
